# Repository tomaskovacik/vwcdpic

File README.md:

You can buy boards or finished emu at my store at tindie:

Full backup/mirror of original vwcdpic site is on <a href="https://web.archive.org/web/20110817024153/http://www.k9spud.com/vwcdpic/">archive.org</a>

<a href="https://github.com/tomaskovacik/vwcdpic/blob/master/vwcdpic-2.8pre3.asm">vwcdpic-2.8pre3.asm</a> - latest sourcecode on internet, with my <a href="https://github.com/tomaskovacik/vwcdpic/commits/master/vwcdpic-2.8pre3.asm">fixies</a>
	
<a href="https://raw.githubusercontent.com/tomaskovacik/vwcdpic/master/vwcdpic-3.x-2.7d-RCD300-1-pic12f629.hex">vwcdpic-3.x-2.7d-RCD300-1-pic12f629.hex</a> is only version works with RCD300 head unit(black one, no silver), if it works with other, for which 2.8 didn't, let me know please.

for ipod support look <a href="https://web.archive.org/web/20090427105500/http://www.k9spud.com/vwcdpic/devel/vwcdpic3/flash/">here</a>

<a href="https://web.archive.org/web/20090427105500/http://www.k9spud.com/vwcdpic/devel/vwcdpic-2.7d/ipod-vw-2.1.asm">iPod-VW Firmware v2.1 Source Code</a> - Use this for iPod 3G+ remote control support on most head units

<a href="https://web.archive.org/web/20090427105500/http://www.k9spud.com/vwcdpic/devel/vwcdpic3/flash/ipod-vw-2.2/ipod-vw-2.2.ConcertII_G5-3.x.asm">iPod-VW Firmware v2.2-Concert II Source Code</a> - Use this for iPod 4G/5G remote control support on Audi Concert II head units 

assemble plan for SMD version generated using <a href="https://github.com/openscopeproject/InteractiveHtmlBom">InteractiveHtmlBom</a> is <a href="https://tomaskovacik.github.io/vwcdpic/hw/bom/ibom.html">here</a>

assemble plan for THT version generated using <a href="https://github.com/openscopeproject/InteractiveHtmlBom">InteractiveHtmlBom</a> is <a href="https://tomaskovacik.github.io/vwcdpic/hw/bom_THT/ibom.html">here</a>

notes:
-------
2.8pre3
- better works with audi concert1/chorus1 head unit made by blaupunkt (previous,next CD works)
- switching from CDC to radio back to CDC works on concert1/chorus1
- tested with:
	- audi concert 1(blaupunkt)
	- audi concert 1(philips)
	- audi concert 2
	- chorus1(blaupunkt)
	- Symphony I
	- vw blaupunkt RadioNavigationSystem MCD
	- VW Passat Blaupunkt Gamma (similar to Gamma V)
	- Audi Symphony II BOSE
	- original project <a href="https://web.archive.org/web/20110811154456/http://www.k9spud.com/wiki/VWCDPIC:Compatible_Head_Units">list</a>
	
		- <a href="https://web.archive.org/web/20110811154456/http://www.k9spud.com/wiki/VWCDPIC:Compatible_Head_Units#Volkswagen">Volkswagen</a>
		
			- <a href="https://web.archive.org/web/20110811154456/http://www.k9spud.com/wiki/VWCDPIC:Compatible_Head_Units#New_Beetle">New Beetle</a>
			
			- <a href="https://web.archive.org/web/20110811154456/http://www.k9spud.com/wiki/VWCDPIC:Compatible_Head_Units#Touareg">Touareg</a>
			
			- <a href="https://web.archive.org/web/20110811154456/http://www.k9spud.com/wiki/VWCDPIC:Compatible_Head_Units#Passat_B3.2FB4_.281993.2B.29">Passat B3/B4 (1993+)</a>
			
			- <a href="https://web.archive.org/web/20110811154456/http://www.k9spud.com/wiki/VWCDPIC:Compatible_Head_Units#EOS_3.2_.282008.29">EOS 3.2 (2008)</a>
			
			- <a href="https://web.archive.org/web/20110811154456/http://www.k9spud.com/wiki/VWCDPIC:Compatible_Head_Units#Single_DIN_Monsoon">Single DIN Monsoon</a>
			
			- <a href="https://web.archive.org/web/20110811154456/http://www.k9spud.com/wiki/VWCDPIC:Compatible_Head_Units#Single_DIN_Monsoon_with_In-Dash_CD_Player">Single DIN Monsoon with In-Dash CD Player</a>
			
			- <a href="https://web.archive.org/web/20110811154456/http://www.k9spud.com/wiki/VWCDPIC:Compatible_Head_Units#Double_DIN_Monsoon">Double DIN Monsoon</a>
			
			- <a href="https://web.archive.org/web/20110811154456/http://www.k9spud.com/wiki/VWCDPIC:Compatible_Head_Units#Multi-Function_Display_.28MFD.29">Multi-Function Display (MFD)</a>
			
			- <a href="https://web.archive.org/web/20110811154456/http://www.k9spud.com/wiki/VWCDPIC:Compatible_Head_Units#Gamma_IV">Gamma IV</a>
			
			- <a href="https://web.archive.org/web/20110811154456/http://www.k9spud.com/wiki/VWCDPIC:Compatible_Head_Units#Gamma_V">Gamma V</a>
			
			- <a href="https://web.archive.org/web/20110811154456/http://www.k9spud.com/wiki/VWCDPIC:Compatible_Head_Units#RCD300">RCD300</a>
			
			- <a href="https://web.archive.org/web/20110811154456/http://www.k9spud.com/wiki/VWCDPIC:Compatible_Head_Units#Blaupunkt_R100">Blaupunkt R100</a>
			
			- <a href="https://web.archive.org/web/20110811154456/http://www.k9spud.com/wiki/VWCDPIC:Compatible_Head_Units#RNS300">RNS300</a>
			
			- <a href="https://web.archive.org/web/20110811154456/http://www.k9spud.com/wiki/VWCDPIC:Compatible_Head_Units#RN_S2_DVD">RN S2 DVD</a>

		- <a href="https://web.archive.org/web/20110811154456/http://www.k9spud.com/wiki/VWCDPIC:Compatible_Head_Units#Seat">Seat</a>
		
			- <a href="https://web.archive.org/web/20110811154456/http://www.k9spud.com/wiki/VWCDPIC:Compatible_Head_Units#Leon">Leon</a>
			
			- <a href="https://web.archive.org/web/20110811154456/http://www.k9spud.com/wiki/VWCDPIC:Compatible_Head_Units#Ibiza">Ibiza</a>

		- <a href="https://web.archive.org/web/20110811154456/http://www.k9spud.com/wiki/VWCDPIC:Compatible_Head_Units#Skoda">Skoda</a>
		
			- <a href="https://web.archive.org/web/20110811154456/http://www.k9spud.com/wiki/VWCDPIC:Compatible_Head_Units#Symphony">Symphony</a>

		- <a href="https://web.archive.org/web/20110811154456/http://www.k9spud.com/wiki/VWCDPIC:Compatible_Head_Units#Audi">Audi</a>
		
			- <a href="https://web.archive.org/web/20110811154456/http://www.k9spud.com/wiki/VWCDPIC:Compatible_Head_Units#Audi_Chorus_II">Audi Chorus II</a>

pinout:
--------------------
| signal        | PIC pin  |
|---------------|----------|
| +5v           | 1 |
| GND           | 8 |
| CLK:          | 7 |
| DataIn:       | 6 |
| DataOut:      | 5 |
| serial 9600:  | 2 |

compile:
---------

http://www.micahcarrick.com/pic-programming-linux.html

for i in `ls *.asm|cut -d\. -f2`;do gpasm vwcdpic-2.$i.asm;done

about connectivity to music players
---------------------------------------------

all what is mentioned in archive on <a href="https://web.archive.org/web/20110817024153/http://www.k9spud.com/vwcdpic/">archive.org</a> should works.

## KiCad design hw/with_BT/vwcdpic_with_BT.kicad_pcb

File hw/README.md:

HW part of vwcdpic project

- made in kicad http://kicad.org
- smd version
- tht version for home manufacture
- for better audio input level, build preamplifier: https://github.com/tomaskovacik/hw/tree/master/kicad/audio_preamplifier

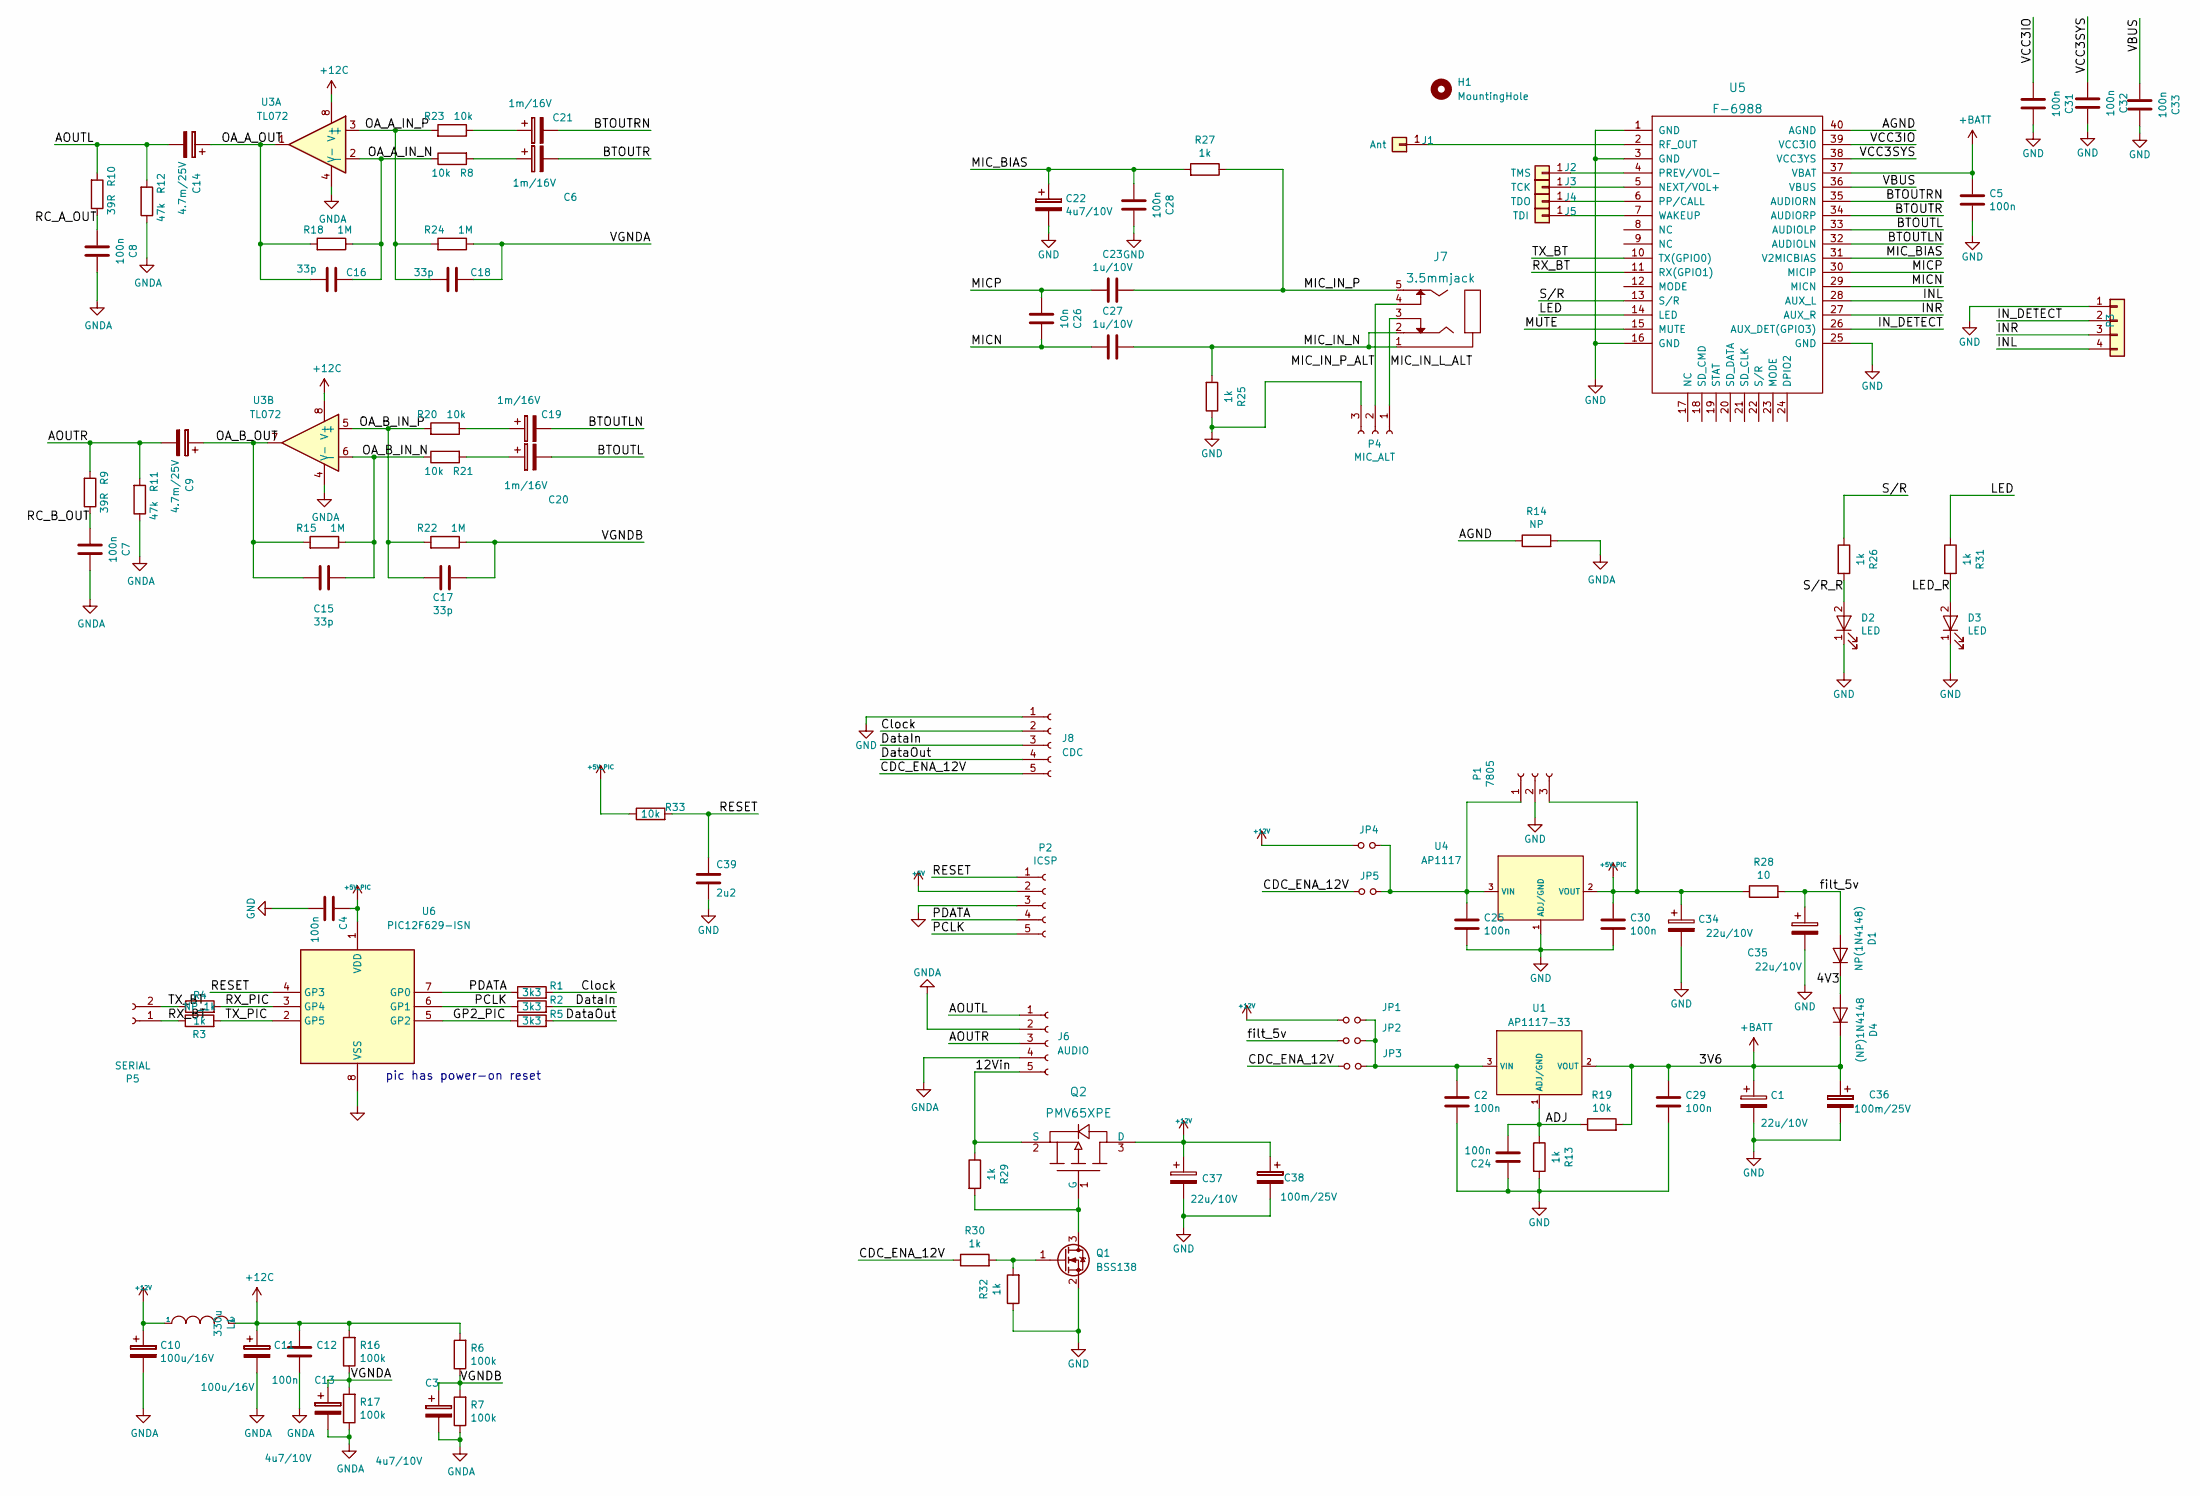
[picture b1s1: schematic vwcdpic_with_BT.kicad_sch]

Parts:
C1, C34, C35, C37: 22u/10V; TantalC_SizeB_EIA-3528_HandSoldering
C2, C4, C5, C7, C8, C12, C24, C25, C28, C29, C30, C31, C32, C33: 100n; C_0805_HandSoldering
C3, C13, C22: 4u7/10V; TantalC_SizeA_EIA-3216_Wave
C6, C19, C20, C21: 1m/16V; c_elec_5x5.8
C9, C14: 4.7m/25V; c_elec_5x5.8
C10, C11: 100u/16V; TantalC_SizeD_EIA-7343_HandSoldering
C15, C16, C17, C18: 33p; C_0805_HandSoldering
C23, C27: 1u/10V; C_1206_HandSoldering
C26: 10n; C_0805_HandSoldering
C36, C38: 100m/25V; c_elec_5x5.8
C39: 2u2; C_1206_HandSoldering
D1: NP(1N4148); MiniMELF_Handsoldering
D2, D3: LED; LED_0805_HandSoldering
D4: (NP)1N4148; MiniMELF_Handsoldering
H1: MountingHole; KM21
J1: Ant; 1pin_smd
J2: TMS; 1pin_smd
J3: TCK; 1pin_smd
J4: TDO; 1pin_smd
J5: TDI; 1pin_smd
J6: AUDIO; Pin_Header_Straight_1x05
J7: 3.5mmjack; 3.5mm_stereo_jack_PJ306M
J8: CDC; Pin_Header_Straight_1x05
JP1, JP2, JP3, JP4, JP5: Jumper_NO_Small; SolderJumper-2_P1.3mm_Open_TrianglePad1.0x1.5mm
L1: 330u; SMD-1210_Pol
P1: 7805; Pin_Header_Straight_1x03
P2: ICSP; Pin_Header_Straight_1x05
P3: AUX; Pin_Header_Straight_1x04
P4: MIC_ALT; Pin_Header_Straight_1x03
P5: SERIAL; Pin_Header_Straight_1x02
Q1: BSS138; SOT-23
Q2: PMV65XPE; SOT-23
R1, R2, R5: 3k3; R_0805_HandSoldering
R3, R13, R25, R26, R27, R29, R30, R31, R32: 1k; R_0805_HandSoldering
R4: NP_1k; R_0805_HandSoldering
R6, R7, R16, R17: 100k; R_0805_HandSoldering
R8, R19, R20, R21, R23, R33: 10k; R_0805_HandSoldering
R9, R10: 39R; R_0805_HandSoldering
R11, R12: 47k; R_0805_HandSoldering
R14: NP; R_0805_HandSoldering
R15, R18, R22, R24: 1M; R_0805_HandSoldering
R28: 10; R_0805_HandSoldering
U1: AP1117-33; AB2_SOT223
U3: TL072; SOIC-8-N
U4: AP1117; AB2_SOT223
U5: F-6988
U6: PIC12F629-ISN; SOIC-8-W_long_pads

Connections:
+12C: C11.1, C12.1, L1.2, R6.2, R16.2, U3.8 (V+)
+12V: C10.1, C37.1, C38.1, JP1.1, JP4.1, L1.1, Q2.3 (D)
+BATT: C1.1, C5.1, C29.1, C36.1, D4.1 (K), R19.2, U1.2 (VOUT), U5.37 (VBAT)
/4V3: D1.1 (K), D4.2 (A)
/12Vin: J6.5, Q2.2 (S), R29.1
/ADJ: C24.2, R13.1, R19.1, U1.1 (ADJ/GND)
/AGND: R14.1, U5.40 (AGND)
/AOUTL: C14.2, J6.1, R10.2, R12.2
/AOUTR: C9.2, J6.3, R9.2, R11.2
/BTOUTL: C20.2, U5.33 (AUDIOLP)
/BTOUTLN: C19.2, U5.32 (AUDIOLN)
/BTOUTR: C6.2, U5.34 (AUDIORP)
/BTOUTRN: C21.2, U5.35 (AUDIORN)
/CDC_ENA_12V: J8.5, JP3.1, JP5.1, R30.1
/Clock: J8.2, R1.2
/DataIn: J8.3, R2.2
/DataOut: J8.4, R5.2
/GP2_PIC: R5.1, U6.5 (GP2)
/INL: P3.4, U5.28 (AUX_L)
/INR: P3.3, U5.27 (AUX_R)
/IN_DETECT: P3.2, U5.26 (AUX_DET(GPIO3))
/LED: R31.1, U5.14 (LED)
/LED_R: D3.2 (A), R31.2
/MICN: C26.2, C27.1, U5.29 (MICN)
/MICP: C23.1, C26.1, U5.30 (MICIP)
/MIC_BIAS: C22.1, C28.1, R27.2, U5.31 (V2MICBIAS)
/MIC_IN_L_ALT: J7.3, P4.1
/MIC_IN_N: C27.2, J7.1, J7.2, R25.2
/MIC_IN_P: C23.2, J7.5, R27.1
/MIC_IN_P_ALT: J7.4, P4.2
/MUTE: U5.15 (MUTE)
/OA_A_IN_N: C16.2, R8.1, R18.1, U3.2 (-)
/OA_A_IN_P: C18.1, R23.2, R24.2, U3.3 (+)
/OA_A_OUT: C14.1, C16.1, R18.2, U3.1
/OA_B_IN_N: C15.2, R15.1, R21.1, U3.6 (-)
/OA_B_IN_P: C17.1, R20.2, R22.2, U3.5 (+)
/OA_B_OUT: C9.1, C15.1, R15.2, U3.7
/PCLK: P2.5, R2.1, U6.6 (GP1)
/PDATA: P2.4, R1.1, U6.7 (GP0)
/RC_A_OUT: C8.1, R10.1
/RC_B_OUT: C7.1, R9.1
/RESET: C39.1, P2.1, R33.2, U6.4 (GP3)
/RX_BT: P5.1, R3.1, U5.11 (RX(GPIO1))
/RX_PIC: R4.2, U6.3 (GP4)
/S/R: R26.1, U5.13 (S/R)
/S/R_R: D2.2 (A), R26.2
/TX_BT: P5.2, R4.1, U5.10 (TX(GPIO0))
/TX_PIC: R3.2, U6.2 (GP5)
/VBUS: C33.1, U5.36 (VBUS)
/VCC3IO: C31.1, U5.39 (VCC3IO)
/VCC3SYS: C32.1, U5.38 (VCC3YS)
/VGNDA: C13.1, C18.2, R16.1, R17.2, R24.1
/VGNDB: C3.1, C17.2, R6.1, R7.2, R22.1
/filt_5v: C35.1, D1.2 (A), JP2.1, R28.2
GND: C1.2, C2.2, C4.2, C5.2, C22.2, C24.1, C25.2, C28.2, C29.2, C30.2, C31.2, C32.2, C33.2, C34.2, C35.2, C36.2, C37.2, C38.2, C39.2, D2.1 (K), D3.1 (K), J8.1, P1.2, P2.3, P3.1, P4.3, Q1.2 (S), R13.2, R25.1, R32.1, U4.1 (ADJ/GND), U5.1 (GND), U5.3 (GND), U5.16 (GND), U5.25 (GND), U6.8 (VSS)
GNDA: C3.2, C7.2, C8.2, C10.2, C11.2, C12.2, C13.2, J6.2, J6.4, R7.1, R11.1, R12.1, R14.2, R17.1, U3.4 (V-)
unnamed: C2.1, JP1.2, JP2.2, JP3.2, U1.3 (VIN)
unnamed: C6.1, R8.2
unnamed: C19.1, R20.1
unnamed: C20.1, R21.2
unnamed: C21.1, R23.1
unnamed: C25.1, JP4.2, JP5.2, P1.1, U4.3 (VIN)
unnamed: J1.1, U5.2 (RF_OUT)
unnamed: J2.1, U5.4 (PREV/VOL-)
unnamed: J3.1, U5.5 (NEXT/VOL+)
unnamed: J4.1, U5.6 (PP/CALL)
unnamed: J5.1, U5.7 (WAKEUP)
unnamed: Q1.1 (G), R30.2, R32.2
unnamed: Q1.3 (D), Q2.1 (G), R29.2

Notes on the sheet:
pic has power-on reset

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
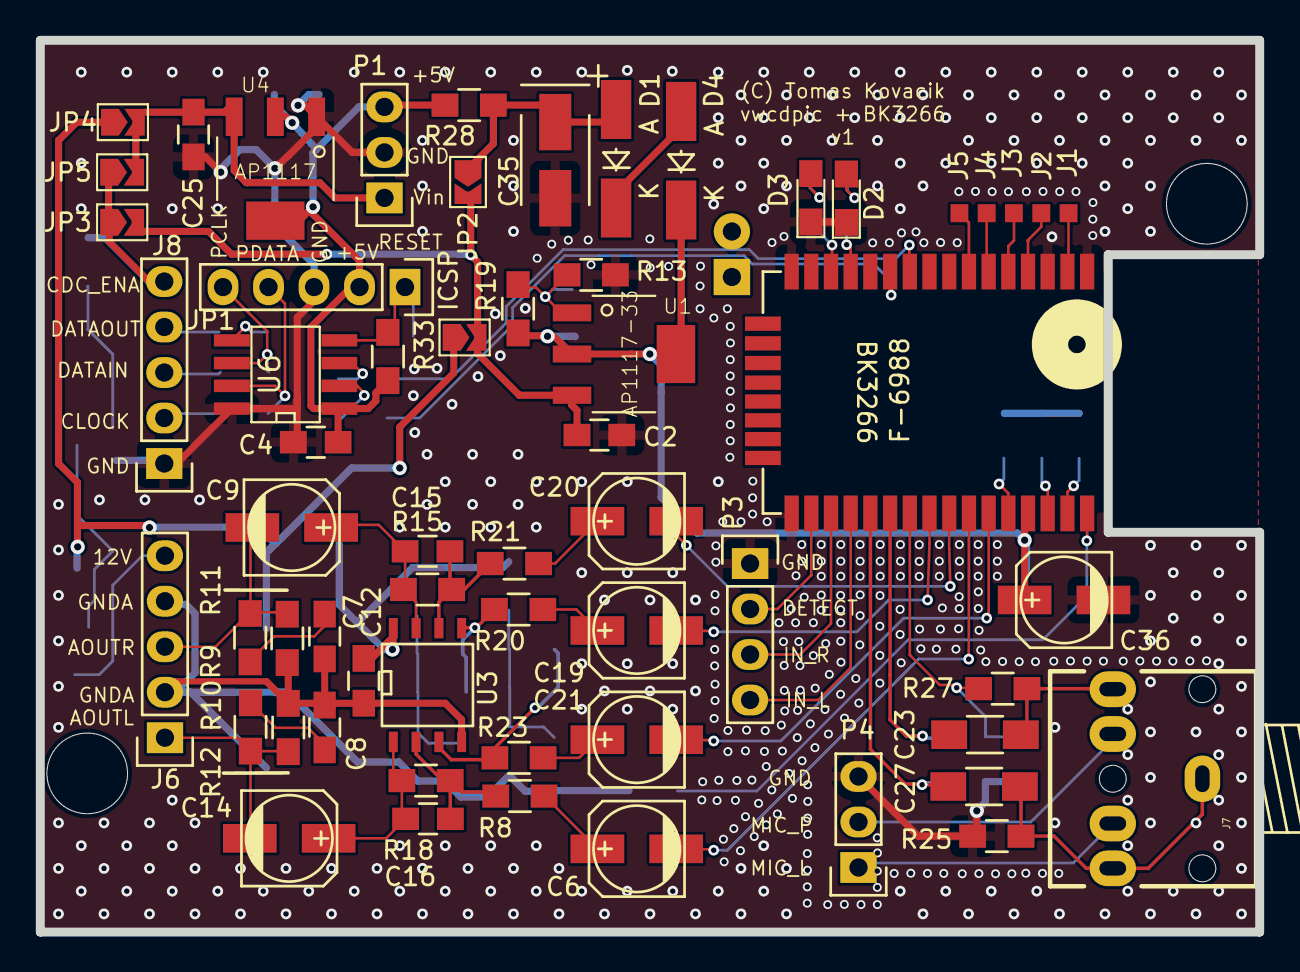
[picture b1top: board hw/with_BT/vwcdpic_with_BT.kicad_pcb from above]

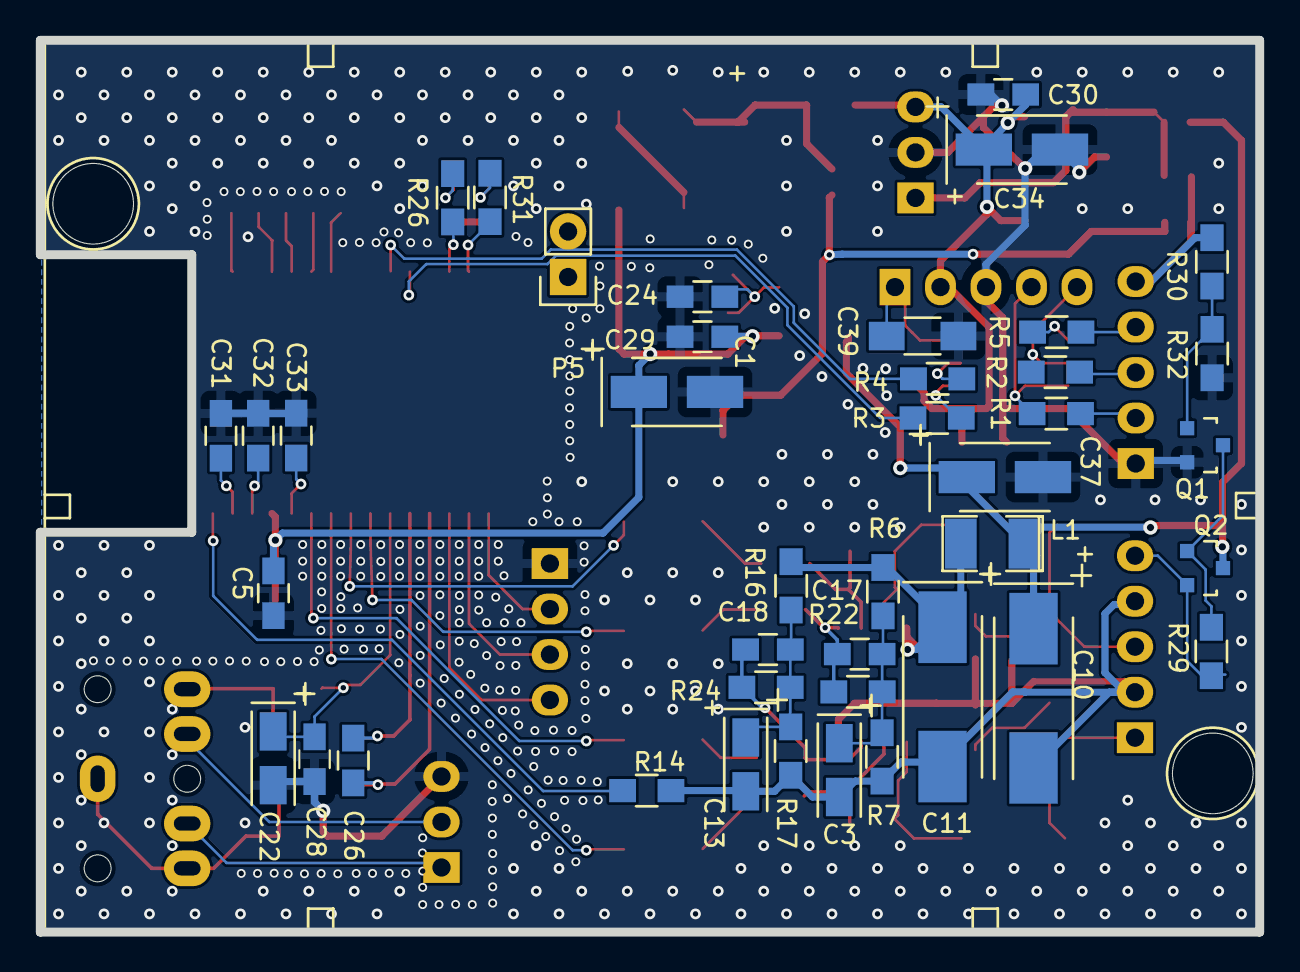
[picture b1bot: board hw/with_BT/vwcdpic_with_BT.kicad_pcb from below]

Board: 2 copper layers, 68.1 x 49.8 mm, 102 parts (42 on the bottom side), 69 nets.

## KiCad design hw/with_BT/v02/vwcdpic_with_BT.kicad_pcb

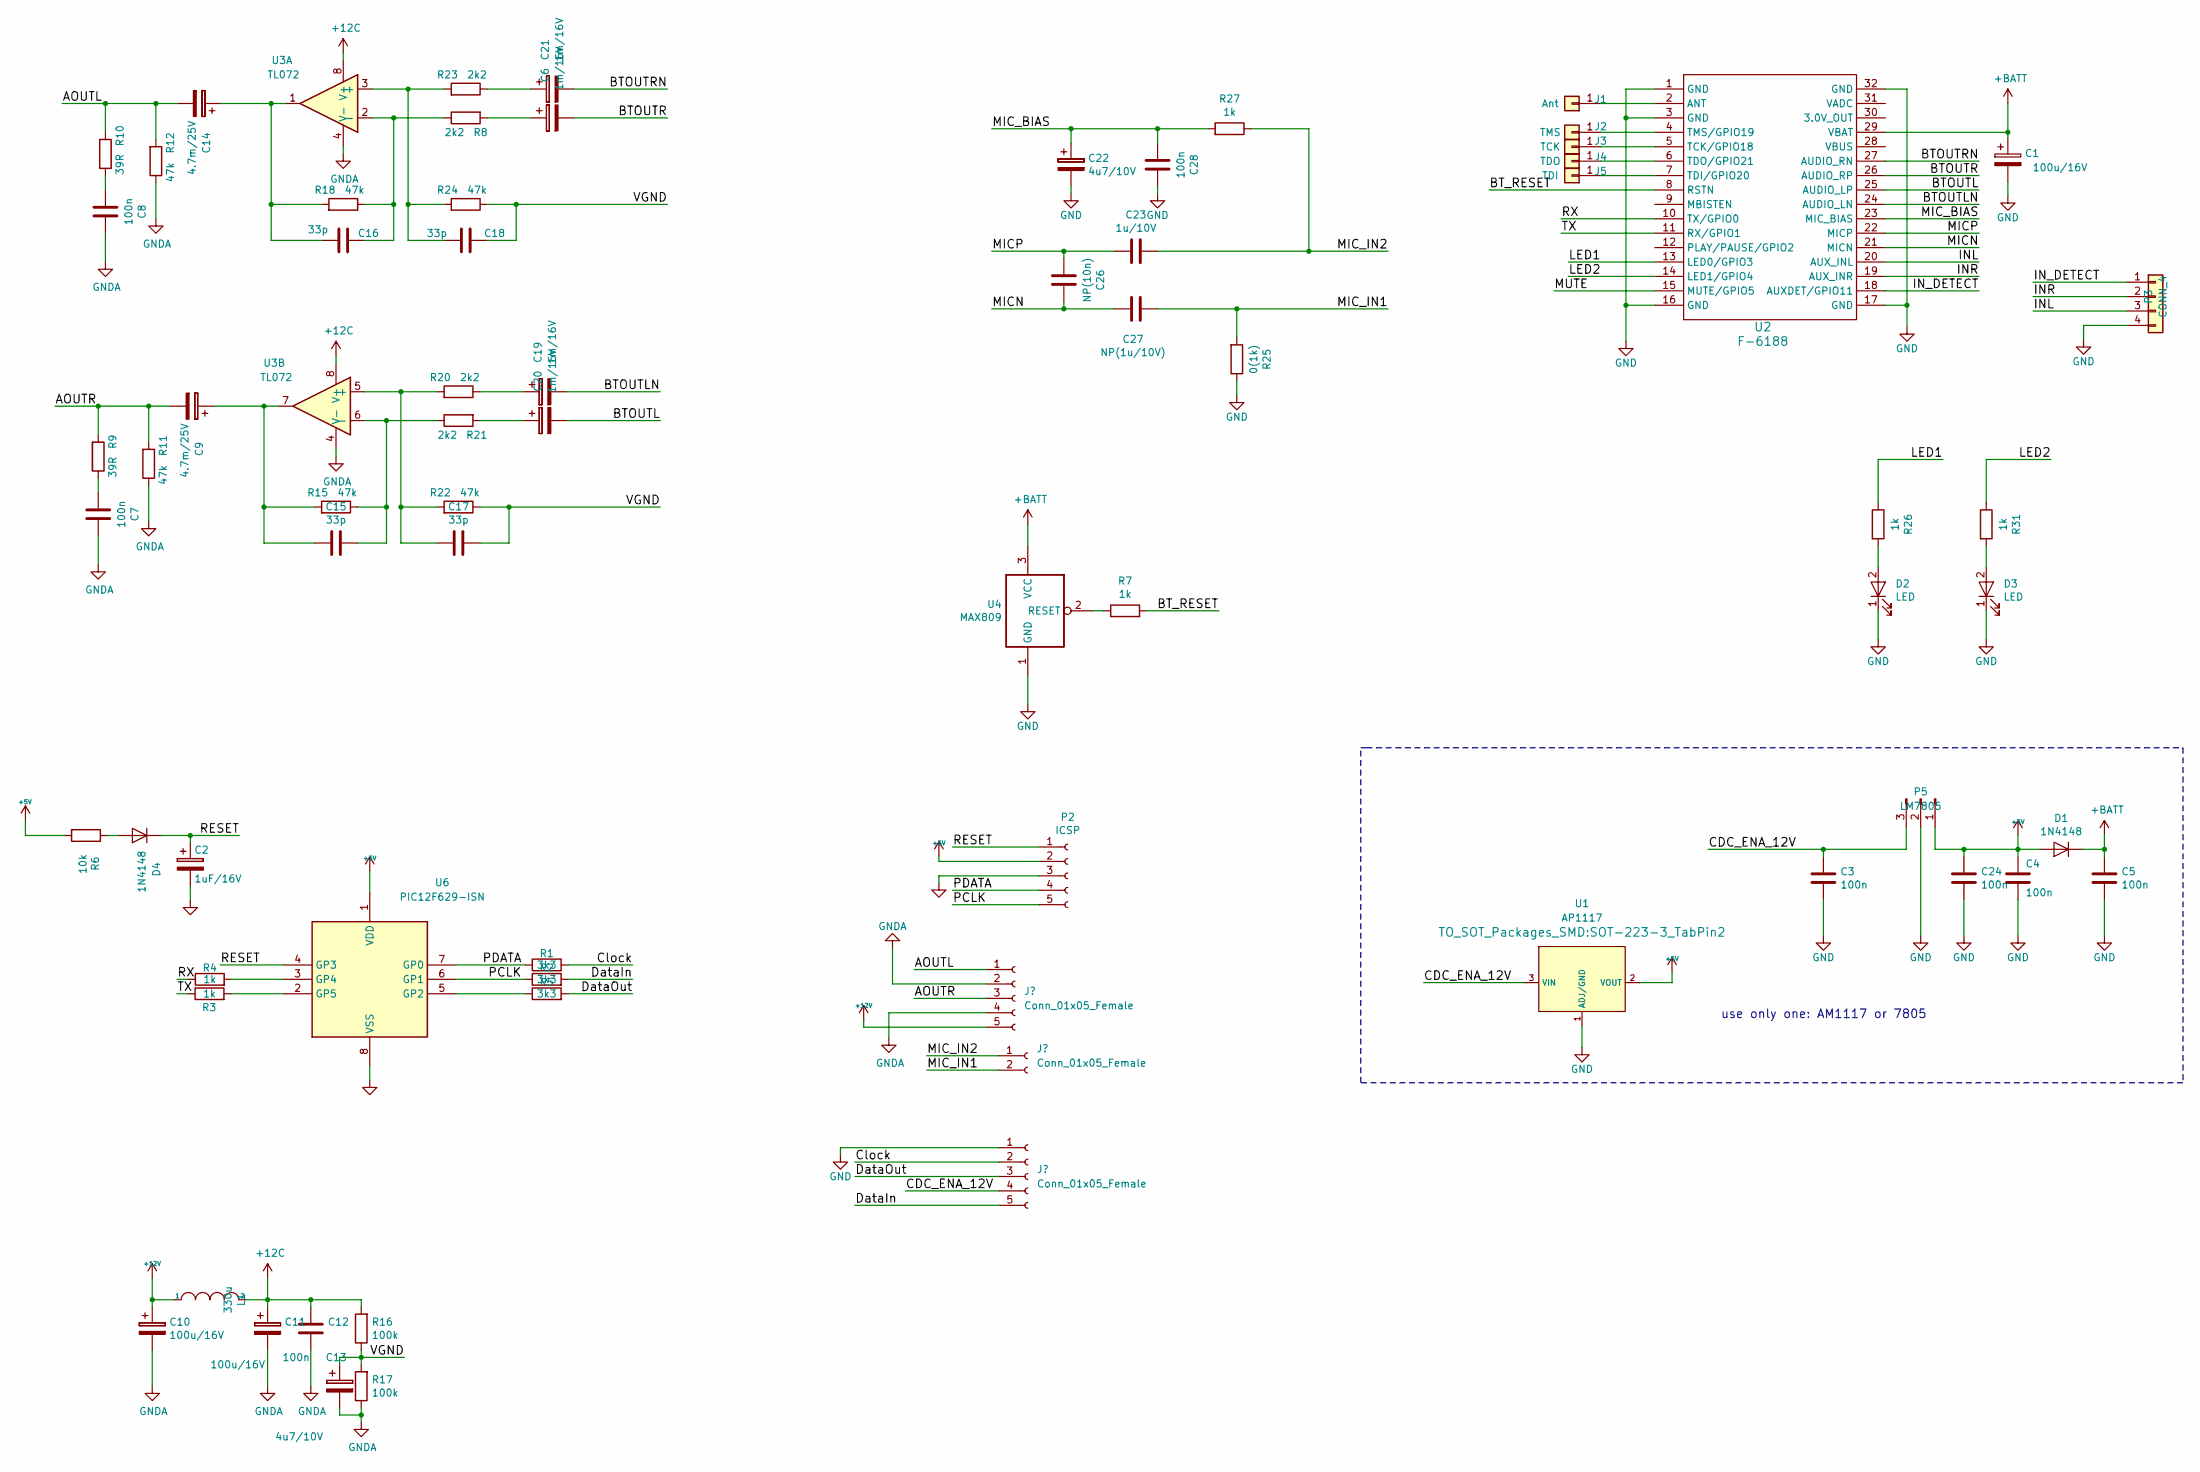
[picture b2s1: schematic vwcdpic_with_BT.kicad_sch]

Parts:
C1: 100u/16V; C_Rect_L7_W2.5_P5
C2: 1uF/16V; C_0805_HandSoldering
C3, C4, C5, C7, C8, C12, C24, C28: 100n; C_0805_HandSoldering
C6, C19, C20, C21: 1m/16V; CP_Elec_5x5.8
C9, C14: 4.7m/25V; c_elec_6.3x5.7
C10, C11: 100u/16V; CP_Tantalum_Case-D_EIA-7343-31_Hand
C13, C22: 4u7/10V; TantalC_SizeA_EIA-3216_Wave
C15, C16, C17, C18: 33p; C_0805_HandSoldering
C23: 1u/10V; C_1206_HandSoldering
C26: NP(10n); C_0805_HandSoldering
C27: NP(1u/10V); C_1206_HandSoldering
D1, D4: 1N4148; D_MiniMELF
D2, D3: LED; LED_0805_HandSoldering
J1: Ant; 1pin_smd
J2: TMS; 1pin_smd
J3: TCK; 1pin_smd
J4: TDO; 1pin_smd
J5: TDI; 1pin_smd
L1: 330u; SMD-1210_Pol
P2: ICSP; Pin_Header_Straight_1x05
P3: CONN_4; Pin_Header_Straight_1x04
P5: LM7805; Pin_Header_Straight_1x03
R1, R2, R5: 3k3; R_0805_HandSoldering
R3, R4, R7, R26, R27, R31: 1k; R_0805_HandSoldering
R6: 10k; R_0805_HandSoldering
R8, R20, R21, R23: 2k2; R_0805_HandSoldering
R9, R10: 39R; R_0805_HandSoldering
R11, R12, R15, R18, R22, R24: 47k; R_0805_HandSoldering
R16, R17: 100k; R_0805_HandSoldering
R25: 0(1k); R_0805_HandSoldering
U1: AP1117; SOT-223-3_TabPin2
U2: F-6188; F-6188_nosilk
U3: TL072; SOIC-8-N
U4: MAX809; SOT-23
U6: PIC12F629-ISN; SOIC-8-W_long_pads

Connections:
+5V: C4.1, C24.1, D1.2 (A), P2.2, P5.1, R6.2, U1.2 (VOUT), U6.1 (VDD)
+12C: C11.1, C12.1, L1.2, R16.2, U3.8 (V+)
+12V: C10.1, L1.1; also elsewhere on the board
+BATT: C1.1, C5.1, D1.1 (K), U2.29 (VBAT), U4.3 (VCC)
/AOUTL: C14.2, R10.2, R12.2; also elsewhere on the board
/AOUTR: C9.2, R9.2, R11.2; also elsewhere on the board
/BTOUTL: C20.2, U2.25 (AUDIO_LP)
/BTOUTLN: C19.2, U2.24 (AUDIO_LN)
/BTOUTR: C6.2, U2.26 (AUDIO_RP)
/BTOUTRN: C21.2, U2.27 (AUDIO_RN)
/BT_RESET: R7.2, U2.8 (RSTN)
/CDC_ENA_12V: C3.1, P5.3, U1.3 (VIN); also elsewhere on the board
/Clock: R1.2; also elsewhere on the board
/DataIn: R2.2; also elsewhere on the board
/DataOut: R5.2; also elsewhere on the board
/INL: P3.3, U2.20 (AUX_INL)
/INR: P3.2, U2.19 (AUX_INR)
/IN_DETECT: P3.1, U2.18 (AUXDET/GPIO11)
/LED1: R26.1, U2.13 (LED0/GPIO3)
/LED2: R31.1, U2.14 (LED1/GPIO4)
/MICN: C26.2, C27.1, U2.21 (MICN)
/MICP: C23.1, C26.1, U2.22 (MICP)
/MIC_BIAS: C22.1, C28.1, R27.2, U2.23 (MIC_BIAS)
/MIC_IN1: C27.2, R25.2; also elsewhere on the board
/MIC_IN2: C23.2, R27.1; also elsewhere on the board
/PCLK: P2.5, R2.1, U6.6 (GP1)
/PDATA: P2.4, R1.1, U6.7 (GP0)
/RESET: C2.1, D4.1 (K), P2.1, U6.4 (GP3)
/RX: R4.1, U2.10 (TX/GPIO0)
/TX: R3.1, U2.11 (RX/GPIO1)
/VGND: C13.1, C17.2, C18.2, R16.1, R17.2, R22.1, R24.1
GND: C1.2, C2.2, C3.2, C4.2, C5.2, C22.2, C24.2, C28.2, D2.1 (K), D3.1 (K), P2.3, P3.4, P5.2, R25.1, U1.1 (ADJ/GND), U2.1 (GND), U2.3 (GND), U2.16 (GND), U2.17 (GND), U2.32 (GND), U4.1 (GND), U6.8 (VSS); also elsewhere on the board
GNDA: C7.2, C8.2, C10.2, C11.2, C12.2, C13.2, R11.1, R12.1, R17.1, U3.4 (V-); also elsewhere on the board
unnamed: C6.1, R8.2
unnamed: C7.1, R9.1
unnamed: C8.1, R10.1
unnamed: C14.1, C16.1, R18.2, U3.1
unnamed: C9.1, C15.1, R15.2, U3.7
unnamed: C15.2, R15.1, R21.1, U3.6 (-)
unnamed: C16.2, R8.1, R18.1, U3.2 (-)
unnamed: C17.1, R20.2, R22.2, U3.5 (+)
unnamed: C18.1, R23.2, R24.2, U3.3 (+)
unnamed: C19.1, R20.1
unnamed: C20.1, R21.2
unnamed: C21.1, R23.1
unnamed: D2.2 (A), R26.2
unnamed: D3.2 (A), R31.2
unnamed: D4.2 (A), R6.1
unnamed: J1.1, U2.2 (ANT)
unnamed: J2.1, U2.4 (TMS/GPIO19)
unnamed: J3.1, U2.5 (TCK/GPIO18)
unnamed: J4.1, U2.6 (TDO/GPIO21)
unnamed: J5.1, U2.7 (TDI/GPIO20)
unnamed: R3.2, U6.2 (GP5)
unnamed: R4.2, U6.3 (GP4)
unnamed: R5.1, U6.5 (GP2)
unnamed: R7.1, U4.2 (RESET)

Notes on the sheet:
use only one: AM1117 or 7805

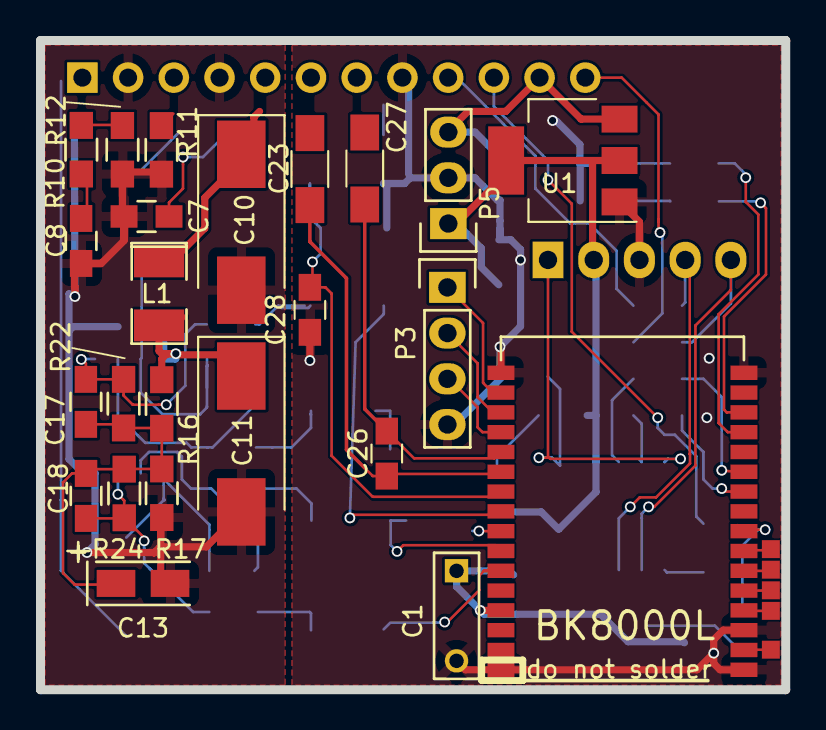
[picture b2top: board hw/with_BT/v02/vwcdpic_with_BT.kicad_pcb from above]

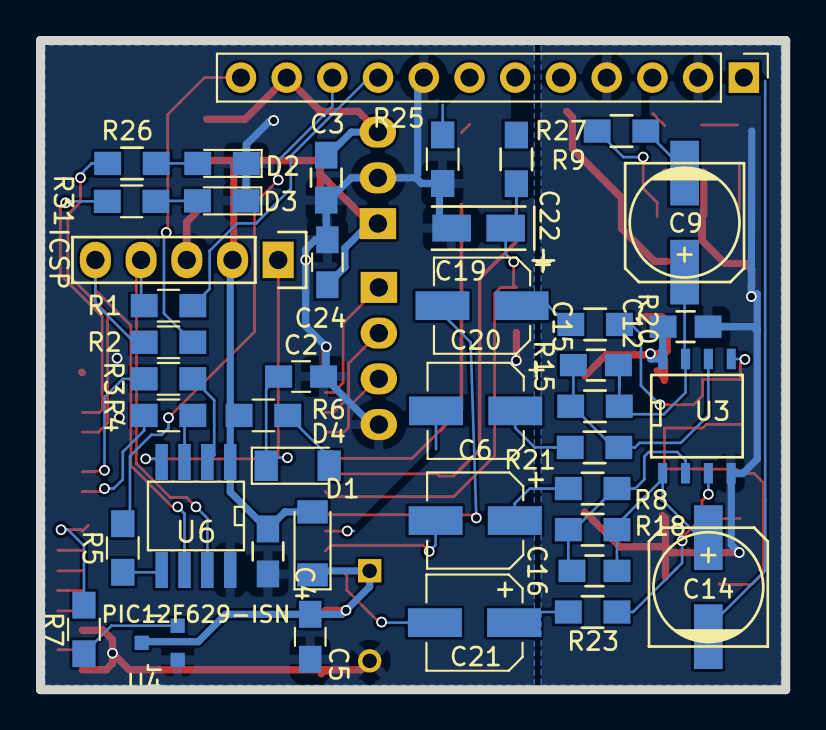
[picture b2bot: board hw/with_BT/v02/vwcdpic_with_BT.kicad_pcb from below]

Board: 2 copper layers, 41.4 x 36.1 mm, 71 parts (42 on the bottom side), 57 nets.

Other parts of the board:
P1: CONN_10; Pin_Header_Straight_1x12_Pitch2.54mm

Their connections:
+12V: P1.5; also elsewhere on the board
/AOUTL: P1.1; also elsewhere on the board
/AOUTR: P1.3; also elsewhere on the board
/CDC_ENA_12V: P1.11; also elsewhere on the board
/Clock: P1.9; also elsewhere on the board
/DataIn: P1.12; also elsewhere on the board
/DataOut: P1.10; also elsewhere on the board
/MIC_IN1: P1.7; also elsewhere on the board
/MIC_IN2: P1.6; also elsewhere on the board
GND: P1.8; also elsewhere on the board
GNDA: P1.2, P1.4; also elsewhere on the board

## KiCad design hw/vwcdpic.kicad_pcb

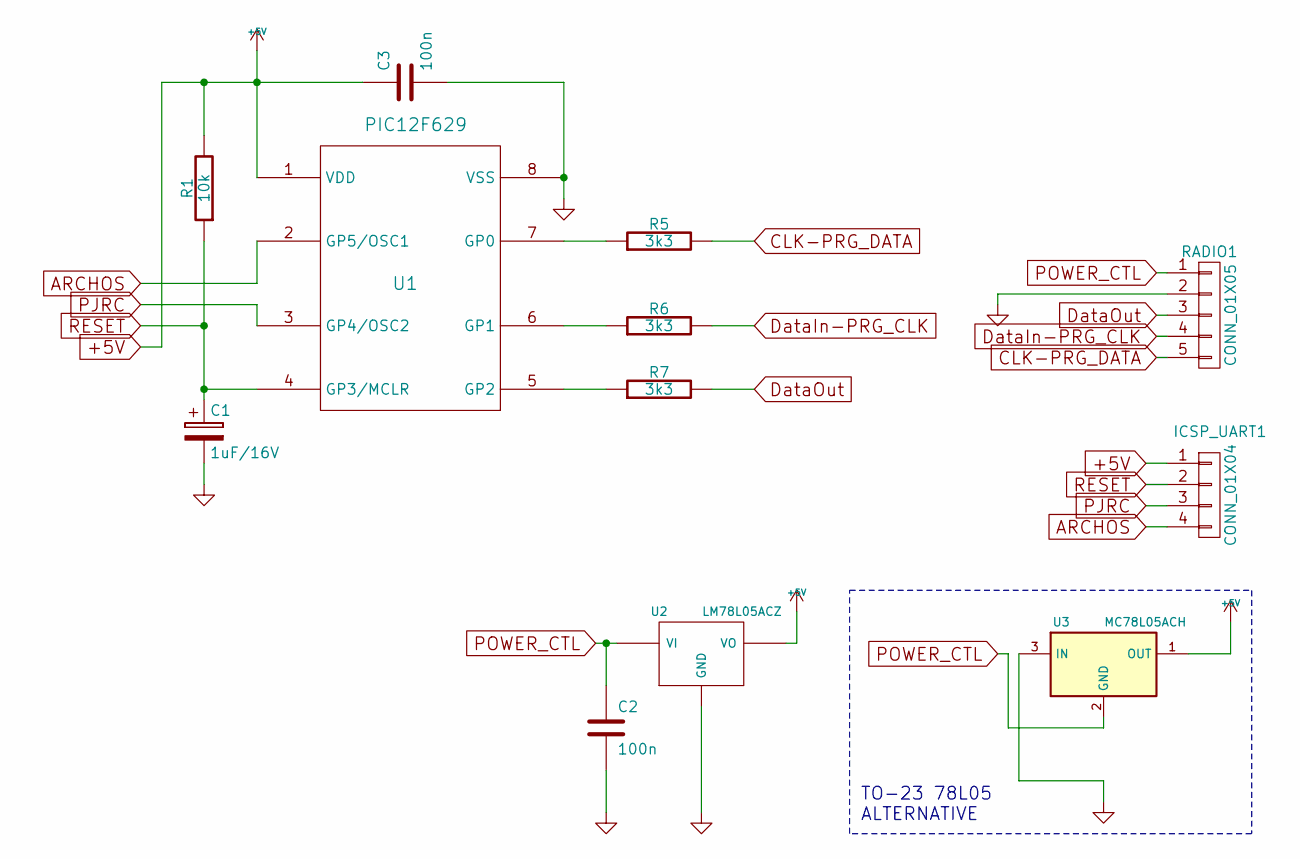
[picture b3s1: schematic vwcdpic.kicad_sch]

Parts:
C1: 1uF/16V; C_0805_HandSoldering
C2, C3: 100n; C_0805
ICSP_UART1: CONN_01X04; Pin_Header_Straight_1x04
R1: 10k; R_0805
R5, R6, R7: 3k3; R_0805
RADIO1: CONN_01X05; Pin_Header_Straight_1x05
U1: PIC12F629; SOIC-8-W_long_pads
U2: LM78L05ACZ; SOT-223-REGULATOR
U3: MC78L05ACH; SOT-23_Handsoldering

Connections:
+5V: C3.1, ICSP_UART1.1, R1.2, U1.1 (VDD), U2.VO, U3.1 (OUT)
ARCHOS: ICSP_UART1.4, U1.2 (GP5/OSC1)
CLK-PRG_DATA: R5.2, RADIO1.5; also elsewhere on the board
DataIn-PRG_CLK: R6.2, RADIO1.4; also elsewhere on the board
DataOut: R7.2, RADIO1.3; also elsewhere on the board
GND: C1.2, C2.2, C3.2, RADIO1.2, U1.8 (VSS), U2.GND, U3.3 (IN); also elsewhere on the board
unnamed: R5.1, U1.7 (GP0)
unnamed: R6.1, U1.6 (GP1)
unnamed: R7.1, U1.5 (GP2)
PJRC: ICSP_UART1.3, U1.3 (GP4/OSC2)
POWER_CTL: C2.1, RADIO1.1, U2.VI, U3.2 (GND); also elsewhere on the board
RESET: C1.1, ICSP_UART1.2, R1.1, U1.4 (GP3/MCLR)

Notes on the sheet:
TO-23 78L05 ALTERNATIVE

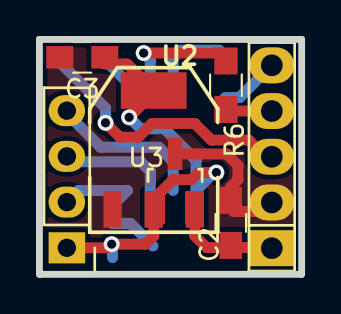
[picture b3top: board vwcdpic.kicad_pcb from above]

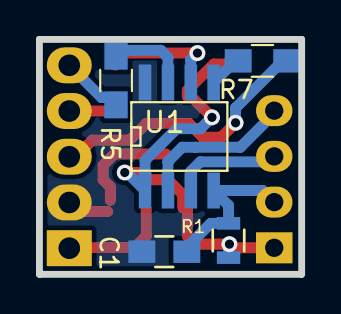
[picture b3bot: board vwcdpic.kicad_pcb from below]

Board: 2 copper layers, 14.6 x 13.1 mm, 12 parts (5 on the bottom side), 12 nets.

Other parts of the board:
RADIO: CONN_01X05; Pin_Header_Straight_1x05

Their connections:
CLK-PRG_DATA: RADIO.5; also elsewhere on the board
DataIn-PRG_CLK: RADIO.4; also elsewhere on the board
DataOut: RADIO.3; also elsewhere on the board
GND: RADIO.2; also elsewhere on the board
POWER_CTL: RADIO.1; also elsewhere on the board

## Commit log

2014-07-02 initial import
2014-07-02 del obsolete files, update Readm
2014-07-02 abimtb unzip
2014-07-03 dafav.sh update
2014-07-03 vwcdpic project files, used in my HW projects, as backup
2014-07-03 fix serial communication for ARCHOS (C4,5,6 didnt work)
2014-07-03 add README.md
2014-07-03 README.md update
2014-11-05 phpmpd2 with touch jukebox and credt support
2014-11-05 cleanup
2014-11-06 bugfix: credit goes to minus with manual refresh after adding song, error mesage apperance config option, credit file config option
2014-11-06 fix credit.php, manual refresh goes to negative credit
2014-11-06 name fix
2015-02-04 readme update about phpMp2
2015-02-05 just some info about how-to connect, serial interface information etc...
2015-02-05 'prev cd' go to CD6 after CD1
2015-02-05 fix swith cd->radio->cd on audi concert1(chorus1)
2015-03-06 README update
2015-03-13 libparadajka moved from googlecode
2015-03-13 README.md
2015-04-30 update about working units
2015-08-24 comment pin fix
2015-08-24 v2/v3 pinouts
2015-08-25 move old files to old dir
2015-10-02 readme udpate
2015-10-02 move from soft repo
2015-10-02 readme for jarex hex files
2015-10-09 original vwcdpic site index file
2015-10-09 hw part
2015-10-09 3dview pics
2015-10-09 update, new schematics file
2015-10-09 moved vwcdpic hw part
2015-10-09 readme tabs fix
2015-10-09 one folder for all old
2015-10-13 ipod 3-4-5gen and 2.7d source code added from archive.org
2015-10-13 move old files to vwcdpic.zip
2015-10-13 remove unneedid dumps
2015-11-19 ignore file
2015-12-10 pictures of assembled unit
2016-01-08 compile 2.8pre3 version for pic12f629
2016-03-09 typo
2016-03-09 pics of build units
2016-03-10 hw upgrade
2016-03-10 pinouts of few radios
2016-03-10 pictures of finished vwcdpic
2016-03-11 remark about version of this asamble plan
2016-03-11 rename
2016-03-21 assembly plans
2016-03-23 enable RESET! test
2016-03-23 try to fix concert 1 turn on, sometimes it's jast hangs
2017-04-19 THT kit assambly plan plus BOM
2017-04-19 remove jarex, as it's just original old code, no his work
2017-04-19 white backgroud
2018-04-25 original license of vwcdpic is GPL2
2018-06-28 fix #1, fix ignoring TP-INFO
2018-06-28 new hex with fixed #1
2018-06-29 Update LICENSE
    original vwcdpic was licensed under GNU GPL v2, so this as it is derivated work is under same license
    https://web.archive.org/web/20110708075240/http://www.k9spud.com//vwcdpic/devel.html
2018-06-29 mv LICENSE LICENSE.md
2018-07-06 fis audi concert1 swithc cd->radio->cd mode
2018-10-26 fix TP
2018-10-26 hw and pictures changes
2018-10-26 pinouts
2020-07-16 ignore cod and lst file
2020-07-16 ignore fp-info-cache and backup files
2020-07-16 removed useless files
2020-07-16 moved to lfs
2020-07-16 add *-bak to gitignore
2020-07-16 updates to svgs
2020-07-16 move to new kicad version
2020-07-16 add sym-lib-table to gitignore
2020-07-16 ibom
2020-07-16 rescue libs storagevwcdpic-rescue.lib
2020-07-16 rm backup files
2020-07-16 new kicad version
2020-07-16 remove spans
2020-07-16 interactive bom link
2020-07-16 rescue-backup folder in gitignore
2021-04-10 ibom for HW version
2021-11-07 Update README.md
    https://forum.kicad.info/t/warning-avoid-all-links-to-kicad-pcb-org-use-kicad-org/31521
2022-04-22 firmware for 12f675
2022-04-22 programing notes
2022-09-17 AT commands support for BK3266 and 12f675 hex
2022-09-17 bk3266 board with pic
2022-09-21 add (C)
2024-07-20 Update README.md
    typo
2026-05-07 removed backups
